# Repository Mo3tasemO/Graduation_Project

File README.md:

# Graduation Project

This repository will be for the Graduation Project.

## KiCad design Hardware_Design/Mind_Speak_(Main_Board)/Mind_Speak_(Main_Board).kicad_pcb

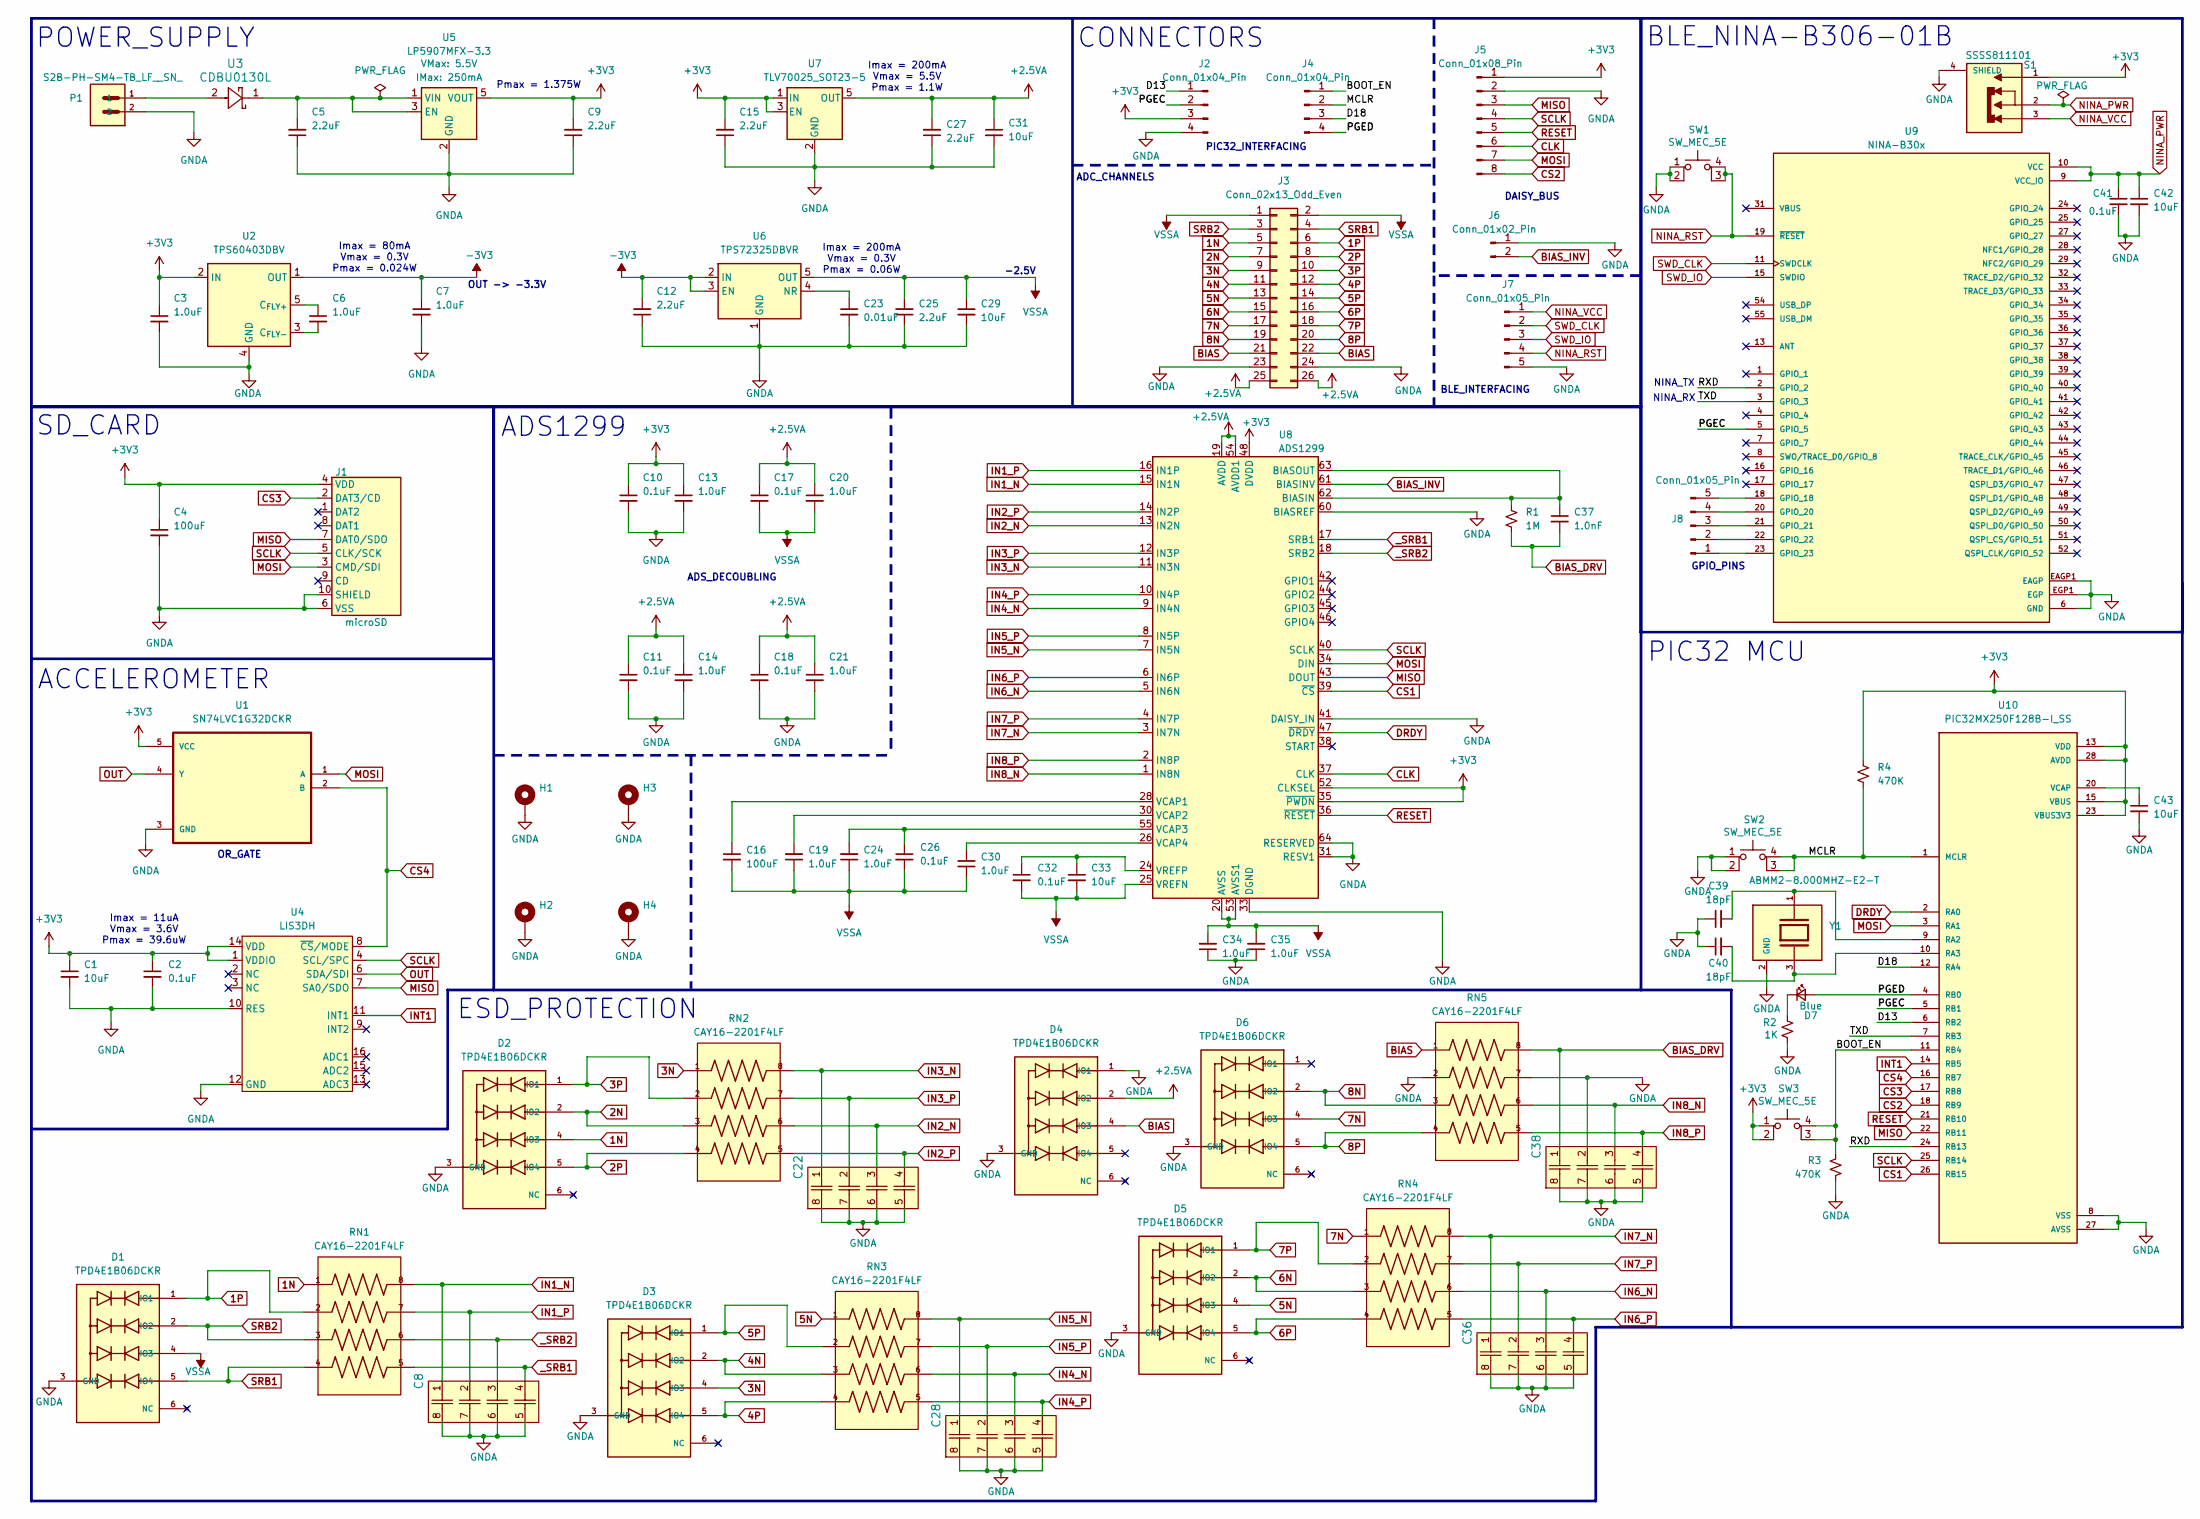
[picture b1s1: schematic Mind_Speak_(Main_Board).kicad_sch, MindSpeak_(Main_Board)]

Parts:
C1, C29, C31, C33, C42, C43: 10uF; C_0603_1608Metric; Voltage 10V; Tolerance 20%
C2, C10, C11, C17, C18, C26, C32, C41: 0.1uF; C_0402_1005Metric; Voltage 16V; Tolerance 10%
C3, C6, C7, C13, C14, C19, C20, C21, C24, C30, C34, C35: 1.0uF; C_0402_1005Metric; Voltage 16V; Tolerance 10%
C4, C16: 100uF; C_1206_3216Metric; Voltage 10V; Tolerance 20%
C5, C9, C12, C15, C25, C27: 2.2uF; C_0402_1005Metric; Voltage 10V; Tolerance 10%
C8, C22, C28, C36, C38: 0.001uF; CKCL44_TDK
C23: 0.01uF; C_0402_1005Metric; Voltage 25V; Tolerance 10%
C37: 1.0nF; C_0402_1005Metric; Voltage 50V; Tolerance 10%
C39, C40: 18pF; C_0402_1005Metric; Voltage 50V; Tolerance 5%
D1, D2, D3, D4, D5, D6: TPD4E1B06DCKR; TVS_TPD4E1B06DCKR; PARTREV C
D7: Blue; LED_0603_1608Metric_Blue
H1, H2, H3, H4: MountingHole_Pad; MountingHole_3.2mm_M3_Pad
J1: microSD; CUI_MSD-1-A
J2, J4: Conn_01x04_Pin; PinHeader_1x04_P2.54mm_Vertical
J3: Conn_02x13_Odd_Even; PinHeader_2x13_P2.54mm_Horizontal
J5: Conn_01x08_Pin; PinHeader_1x08_P2.54mm_Vertical
J6: Conn_01x02_Pin; PinHeader_1x02_P2.54mm_Vertical
J7, J8: Conn_01x05_Pin; PinHeader_1x05_P2.54mm_Vertical
P1: S2B-PH-SM4-TB_LF__SN_; JST_S2B-PH-SM4-TB_LF__SN_
R1: 1M; R_0402_1005Metric
R2: 1K; R_0402_1005Metric
R3, R4: 470K; R_0402_1005Metric
RN1, RN2, RN3, RN4, RN5: CAY16-2201F4LF; RESCAF80P320X160X60-8N
S1: SSSS811101; SW_SSSS811101; PARTREV N/A
SW1, SW2, SW3: SW_MEC_5E; SW_Push_1P1T_NO_Vertical_Wuerth_434133025816
U1: SN74LVC1G32DCKR; SOT65P210X110-5N
U2: TPS60403DBV; SOT-23-5
U3: CDBU0130L; CDBU
U4: LIS3DH; ST_LGA-16_3x3mm_P0.5mm_5x3
U5: LP5907MFX-3.3; SOT23-5
U6: TPS72325DBVR; SOT-23-5
U7: TLV70025_SOT23-5; SOT-23-5
U8: ADS1299; TQFP-64_10x10mm_P0.5mm
U9: NINA-B30x; XCVR_NINA-B306-00B; PARTREV R07
U10: PIC32MX250F128B-I_SS; SOP65P780X200-28N
Y1: ABMM2-8.000MHZ-E2-T; XTAL_ABMM2-8.000MHZ-E2-T; PARTREV 01.18.13

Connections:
1N: D2.4 (IO3), J3.5, RN1.1
1P: D1.1 (IO1), J3.6, RN1.2
2N: D2.2 (IO2), J3.7, RN2.3
2P: D2.5 (IO4), J3.8, RN2.4
3N: D3.4 (IO3), J3.9, RN2.1
3P: D2.1 (IO1), J3.10, RN2.2
4N: D3.2 (IO2), J3.11, RN3.3
4P: D3.5 (IO4), J3.12, RN3.4
5N: D5.4 (IO3), J3.13, RN3.1
5P: D3.1 (IO1), J3.14, RN3.2
6N: D5.2 (IO2), J3.15, RN4.3
6P: D5.5 (IO4), J3.16, RN4.4
7N: D6.4 (IO3), J3.17, RN4.1
7P: D5.1 (IO1), J3.18, RN4.2
8N: D6.2 (IO2), J3.19, RN5.3
8P: D6.5 (IO4), J3.20, RN5.4
+2.5VA: C11.1, C14.1, C17.1, C18.1, C20.1, C21.1, C27.2, C31.1, D4.2 (IO2), J3.25, J3.26, U7.5 (OUT), U8.19 (AVDD), U8.21 (AVDD), U8.22 (AVDD), U8.54 (AVDD1), U8.56 (AVDD), U8.59 (AVDD)
+3V3: C1.1, C2.1, C3.1, C4.1, C9.2, C10.1, C13.1, C15.2, J1.4 (VDD), J2.3, J5.1, R4.2, S1.1, SW3.1, SW3.2, U1.5 (VCC), U2.2 (IN), U4.1 (VDDIO), U4.14 (VDD), U5.5 (VOUT), U7.1 (IN), U7.3 (EN), U8.35 (~PWDN), U8.48 (DVDD), U8.50 (DVDD), U8.52 (CLKSEL), U10.13 (VDD), U10.15 (VBUS), U10.23 (VBUS3V3), U10.28 (AVDD)
-3V3: C7.1, C12.2, U2.1 (OUT), U6.2 (IN), U6.3 (EN)
/BOOT_EN: J4.1, R3.2, SW3.3 (K), SW3.4 (A), U10.11 (RB4)
/D13: J2.1, U10.6 (RB2)
/D18: J4.3, U10.12 (RA4)
/MCLR: J4.2, R4.1, SW2.3 (K), SW2.4 (A), U10.1 (MCLR)
/PGEC: J2.2, U9.5 (GPIO_5), U10.5 (RB1)
/PGED: D7.2 (A), J4.4, U10.4 (RB0)
/RXD: U9.2 (GPIO_2), U10.24 (RB13)
/TXD: U9.3 (GPIO_3), U10.7 (RB3)
BIAS: D4.4 (IO3), J3.21, J3.22, RN5.1
BIAS_DRV: C37.2, C38.1, R1.1, RN5.8
BIAS_INV: J6.2, U8.61 (BIASINV)
CLK: J5.6, U8.37 (CLK)
CS1: U8.39 (~CS), U10.26 (RB15)
CS2: J5.8, U10.18 (RB9)
CS3: J1.2 (DAT3/CD), U10.17 (RB8)
CS4: U1.2 (B), U4.8 (~CS/MODE), U10.16 (RB7)
DRDY: U8.47 (~DRDY), U10.2 (RA0)
GNDA: C1.2, C2.2, C3.2, C4.2, C5.1, C7.2, C8.5, C8.6, C8.7, C8.8, C9.1, C10.2, C11.2, C12.1, C13.2, C14.2, C15.1, C18.2, C21.2, C22.5, C22.6, C22.7, C22.8, C23.2, C25.1, C27.1, C28.5, C28.6, C28.7, C28.8, C29.2, C31.2, C34.1, C35.1, C36.5, C36.6, C36.7, C36.8, C38.2, C38.5, C38.6, C38.7, C38.8, C39.1, C40.1, C41.2, C42.2, C43.2, D1.3 (GND), D2.3 (GND), D3.3 (GND), D4.1 (IO1), D4.3 (GND), D5.3 (GND), D6.3 (GND), H1.1 (1_1), H2.1 (1_1), H3.1 (1_1), H4.1 (1_1), J1.6 (VSS), J1.10 (SHIELD), J2.4, J3.23, J3.24, J5.2, J6.1, J7.5, P1.2, R2.1, R3.1, RN5.2, RN5.7, S1.4 (SHIELD_4), SW1.1, SW1.2, SW2.1, SW2.2, U1.3 (GND), U2.4 (GND), U4.5 (GND), U4.10 (RES), U4.12 (GND), U5.2 (GND), U6.1 (GND), U7.2 (GND), U8.31 (RESV1), U8.33 (DGND), U8.41 (DAISY_IN), U8.49 (DGND), U8.51 (DGND), U8.60 (BIASREF), U8.64 (RESERVED), U9.6 (GND), U9.12 (GND), U9.14 (GND), U9.26 (GND), U9.30 (GND), U9.53 (GND), U9.EAGP1 (EAGP), U9.EAGP2 (EAGP), U9.EAGP3 (EAGP), U9.EAGP4 (EAGP), U9.EGP1 (EGP), U9.EGP2 (EGP), U9.EGP3 (EGP), U9.EGP4 (EGP), U9.EGP5 (EGP), U9.EGP6 (EGP), U9.EGP7 (EGP), U9.EGP8 (EGP), U9.EGP9 (EGP), U9.EGP10 (EGP), U9.EGP11 (EGP), U9.EGP12 (EGP), U10.8 (VSS), U10.19 (VSS), U10.27 (AVSS), Y1.2 (GND), Y1.4 (GND)
IN1_N: C8.1, RN1.8, U8.15 (IN1N)
IN1_P: C8.2, RN1.7, U8.16 (IN1P)
IN2_N: C22.3, RN2.6, U8.13 (IN2N)
IN2_P: C22.4, RN2.5, U8.14 (IN2P)
IN3_N: C22.1, RN2.8, U8.11 (IN3N)
IN3_P: C22.2, RN2.7, U8.12 (IN3P)
IN4_N: C28.3, RN3.6, U8.9 (IN4N)
IN4_P: C28.4, RN3.5, U8.10 (IN4P)
IN5_N: C28.1, RN3.8, U8.7 (IN5N)
IN5_P: C28.2, RN3.7, U8.8 (IN5P)
IN6_N: C36.3, RN4.6, U8.5 (IN6N)
IN6_P: C36.4, RN4.5, U8.6 (IN6P)
IN7_N: C36.1, RN4.8, U8.3 (IN7N)
IN7_P: C36.2, RN4.7, U8.4 (IN7P)
IN8_N: C38.3, RN5.6, U8.1 (IN8N)
IN8_P: C38.4, RN5.5, U8.2 (IN8P)
INT1: U4.11 (INT1), U10.14 (RB5)
MISO: J1.7 (DAT0/SDO), J5.3, U4.7 (SA0/SDO), U8.43 (DOUT), U10.22 (RB11)
MOSI: J1.3 (CMD/SDI), J5.7, U1.1 (A), U8.34 (DIN), U10.3 (RA1)
NINA_PWR: C41.1, C42.1, S1.2, U9.9 (VCC_IO), U9.10 (VCC)
NINA_RST: J7.4, SW1.3 (K), SW1.4 (A), U9.19 (~RESET)
NINA_VCC: J7.1, S1.3
unnamed: D7.1 (K), R2.2
unnamed: J8.1, U9.23 (GPIO_23)
unnamed: J8.2, U9.22 (GPIO_22)
unnamed: J8.3, U9.21 (GPIO_21)
unnamed: J8.4, U9.20 (GPIO_20)
unnamed: J8.5, U9.18 (GPIO_18)
unnamed: P1.1, U3.2
unnamed: C6.1, U2.5 (C_{FLY+})
unnamed: C6.2, U2.3 (C_{FLY-})
unnamed: C5.2, U3.1, U5.1 (VIN), U5.3 (EN)
unnamed: C23.1, U6.4 (NR)
unnamed: C37.1, R1.2, U8.62 (BIASIN), U8.63 (BIASOUT)
unnamed: C16.1, U8.28 (VCAP1)
unnamed: C19.2, U8.30 (VCAP2)
unnamed: C24.2, C26.1, U8.55 (VCAP3)
unnamed: C30.2, U8.26 (VCAP4)
unnamed: C32.1, C33.1, U8.24 (VREFP)
unnamed: C39.2, U10.9 (RA2), Y1.1
unnamed: C40.2, U10.10 (RA3), Y1.3
unnamed: C43.1, U10.20 (VCAP)
OUT: U1.4 (Y), U4.6 (SDA/SDI)
RESET: J5.5, U8.36 (~RESET), U10.21 (RB10)
SCLK: J1.5 (CLK/SCK), J5.4, U4.4 (SCL/SPC), U8.40 (SCLK), U10.25 (RB14)
SRB1: D1.5 (IO4), J3.4, RN1.4
SRB2: D1.2 (IO2), J3.3, RN1.3
SWD_CLK: J7.2, U9.11 (SWDCLK)
SWD_IO: J7.3, U9.15 (SWDIO)
VSSA: C16.2, C17.2, C19.1, C20.2, C24.1, C25.2, C26.2, C29.1, C30.1, C32.2, C33.2, C34.2, C35.2, D1.4 (IO3), J3.1, J3.2, U6.5 (OUT), U8.20 (AVSS), U8.23 (AVSS), U8.25 (VREFN), U8.32 (AVSS), U8.53 (AVSS1), U8.57 (AVSS), U8.58 (AVSS)
_SRB1: C8.4, RN1.5, U8.17 (SRB1)
_SRB2: C8.3, RN1.6, U8.18 (SRB2)

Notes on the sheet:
CONNECTORS
Imax = 11uA Vmax = 3.6V Pmax = 39.6uW
POWER_SUPPLY
ADC_CHANNELS
ACCELEROMETER
Imax = 200mA Vmax = 5.5V Pmax = 1.1W
BLE_NINA-B306-01B
DAISY_BUS
-2.5V
ESD_PROTECTION
Pmax = 1.375W
PIC32_INTERFACING
NINA_RX
BLE_INTERFACING
ADS1299
Imax = 200mA Vmax = 0.3V Pmax = 0.06W
Imax = 80mA Vmax = 0.3V Pmax = 0.024W
SD_CARD
ADS_DECOUBLING
OR_GATE
OUT -> -3.3V
NINA_TX
GPIO_PINS
PIC32 MCU

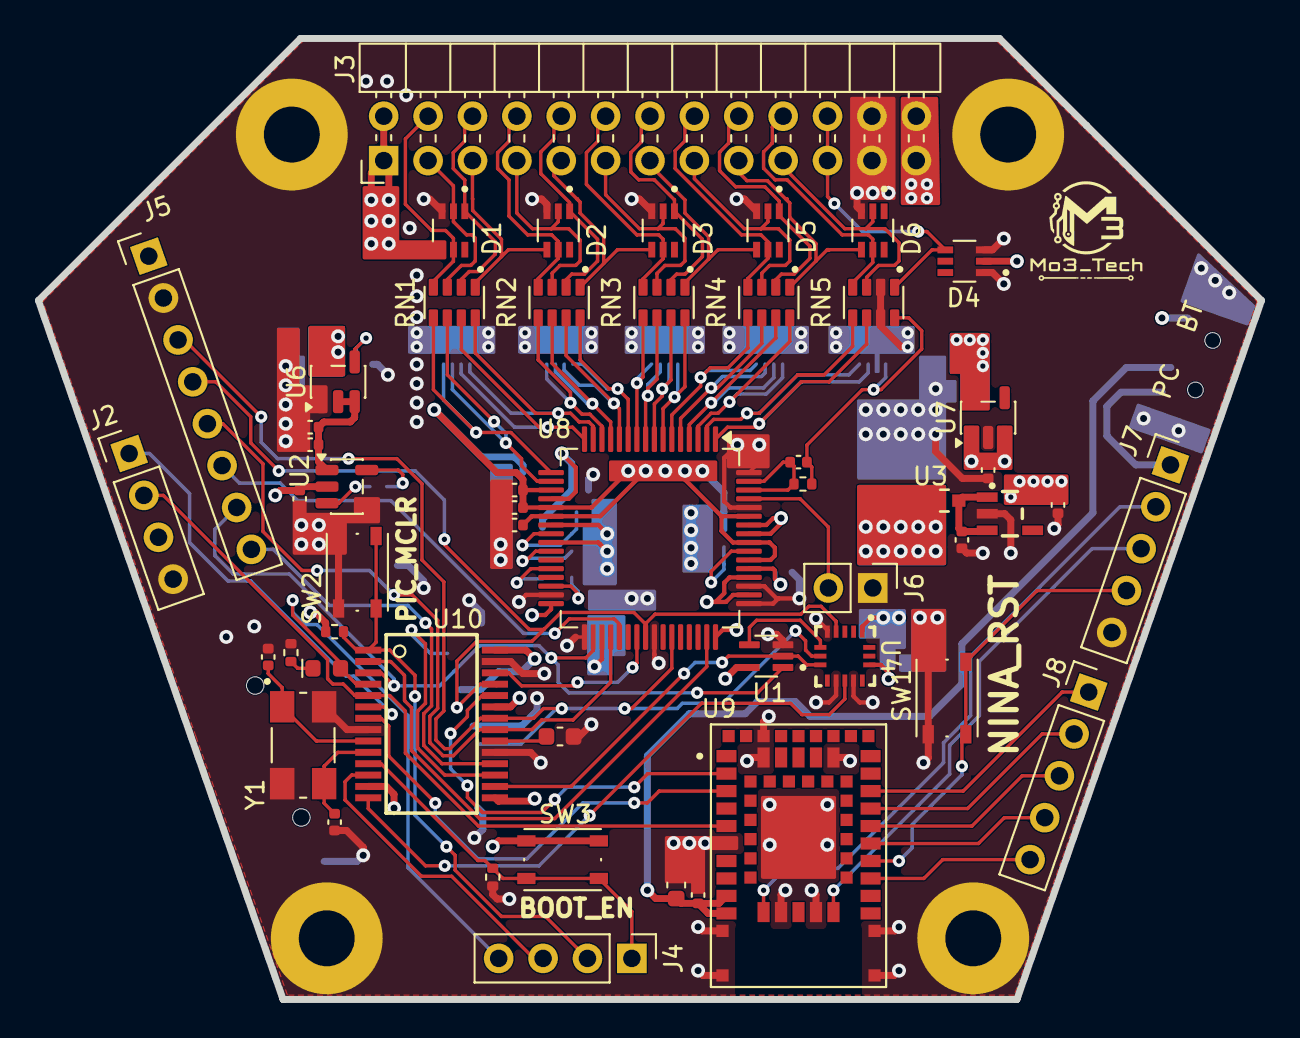
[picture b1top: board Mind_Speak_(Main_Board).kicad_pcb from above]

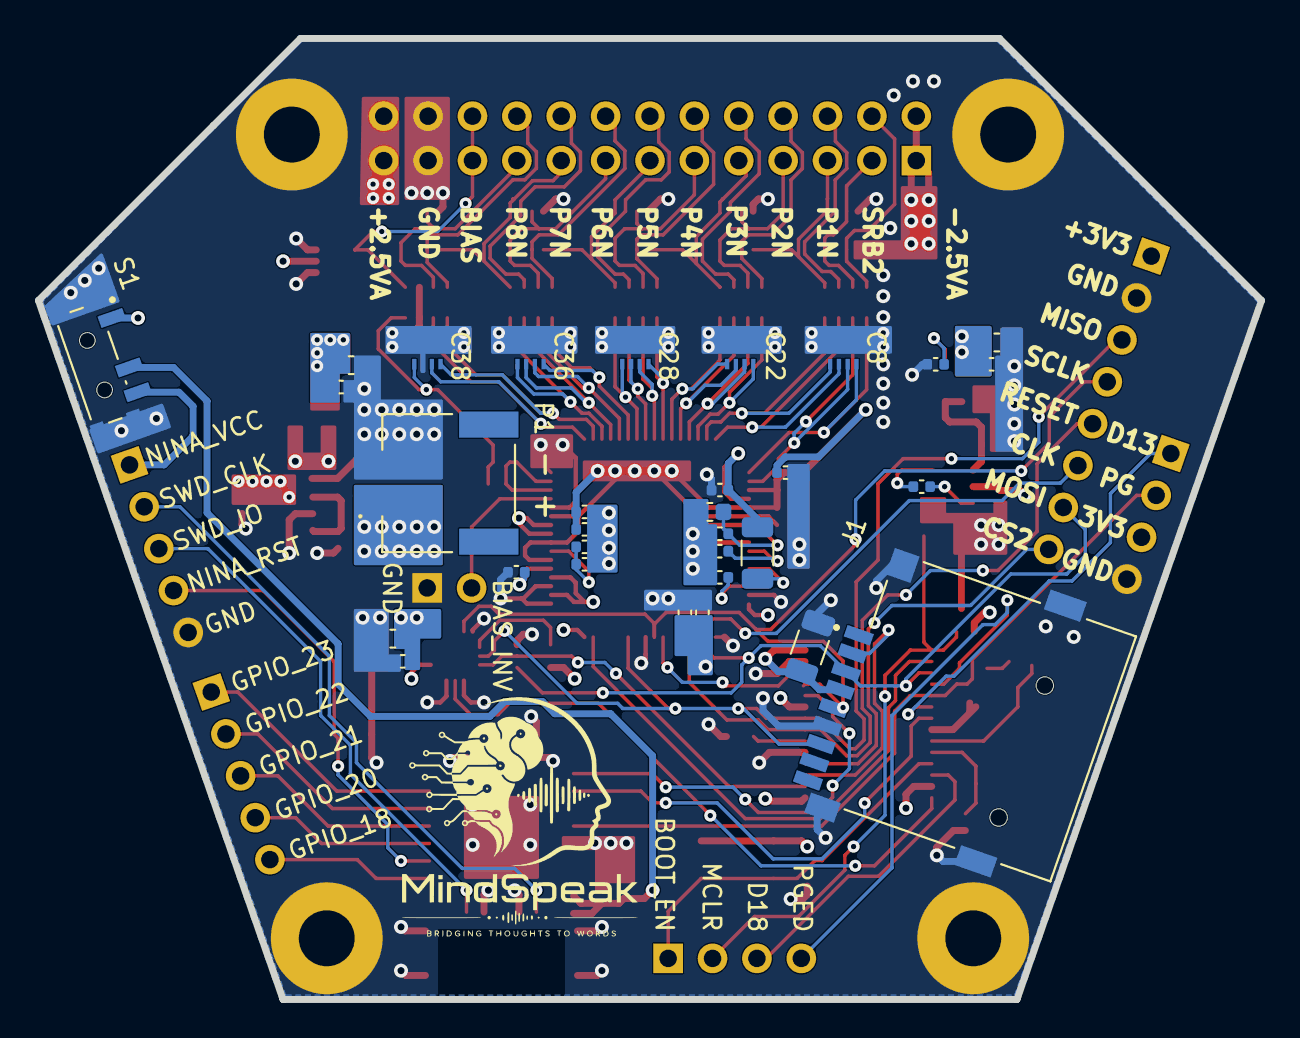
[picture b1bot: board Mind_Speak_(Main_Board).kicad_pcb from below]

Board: 4 copper layers, 70.0 x 55.0 mm, 87 parts (31 on the bottom side), 89 nets.

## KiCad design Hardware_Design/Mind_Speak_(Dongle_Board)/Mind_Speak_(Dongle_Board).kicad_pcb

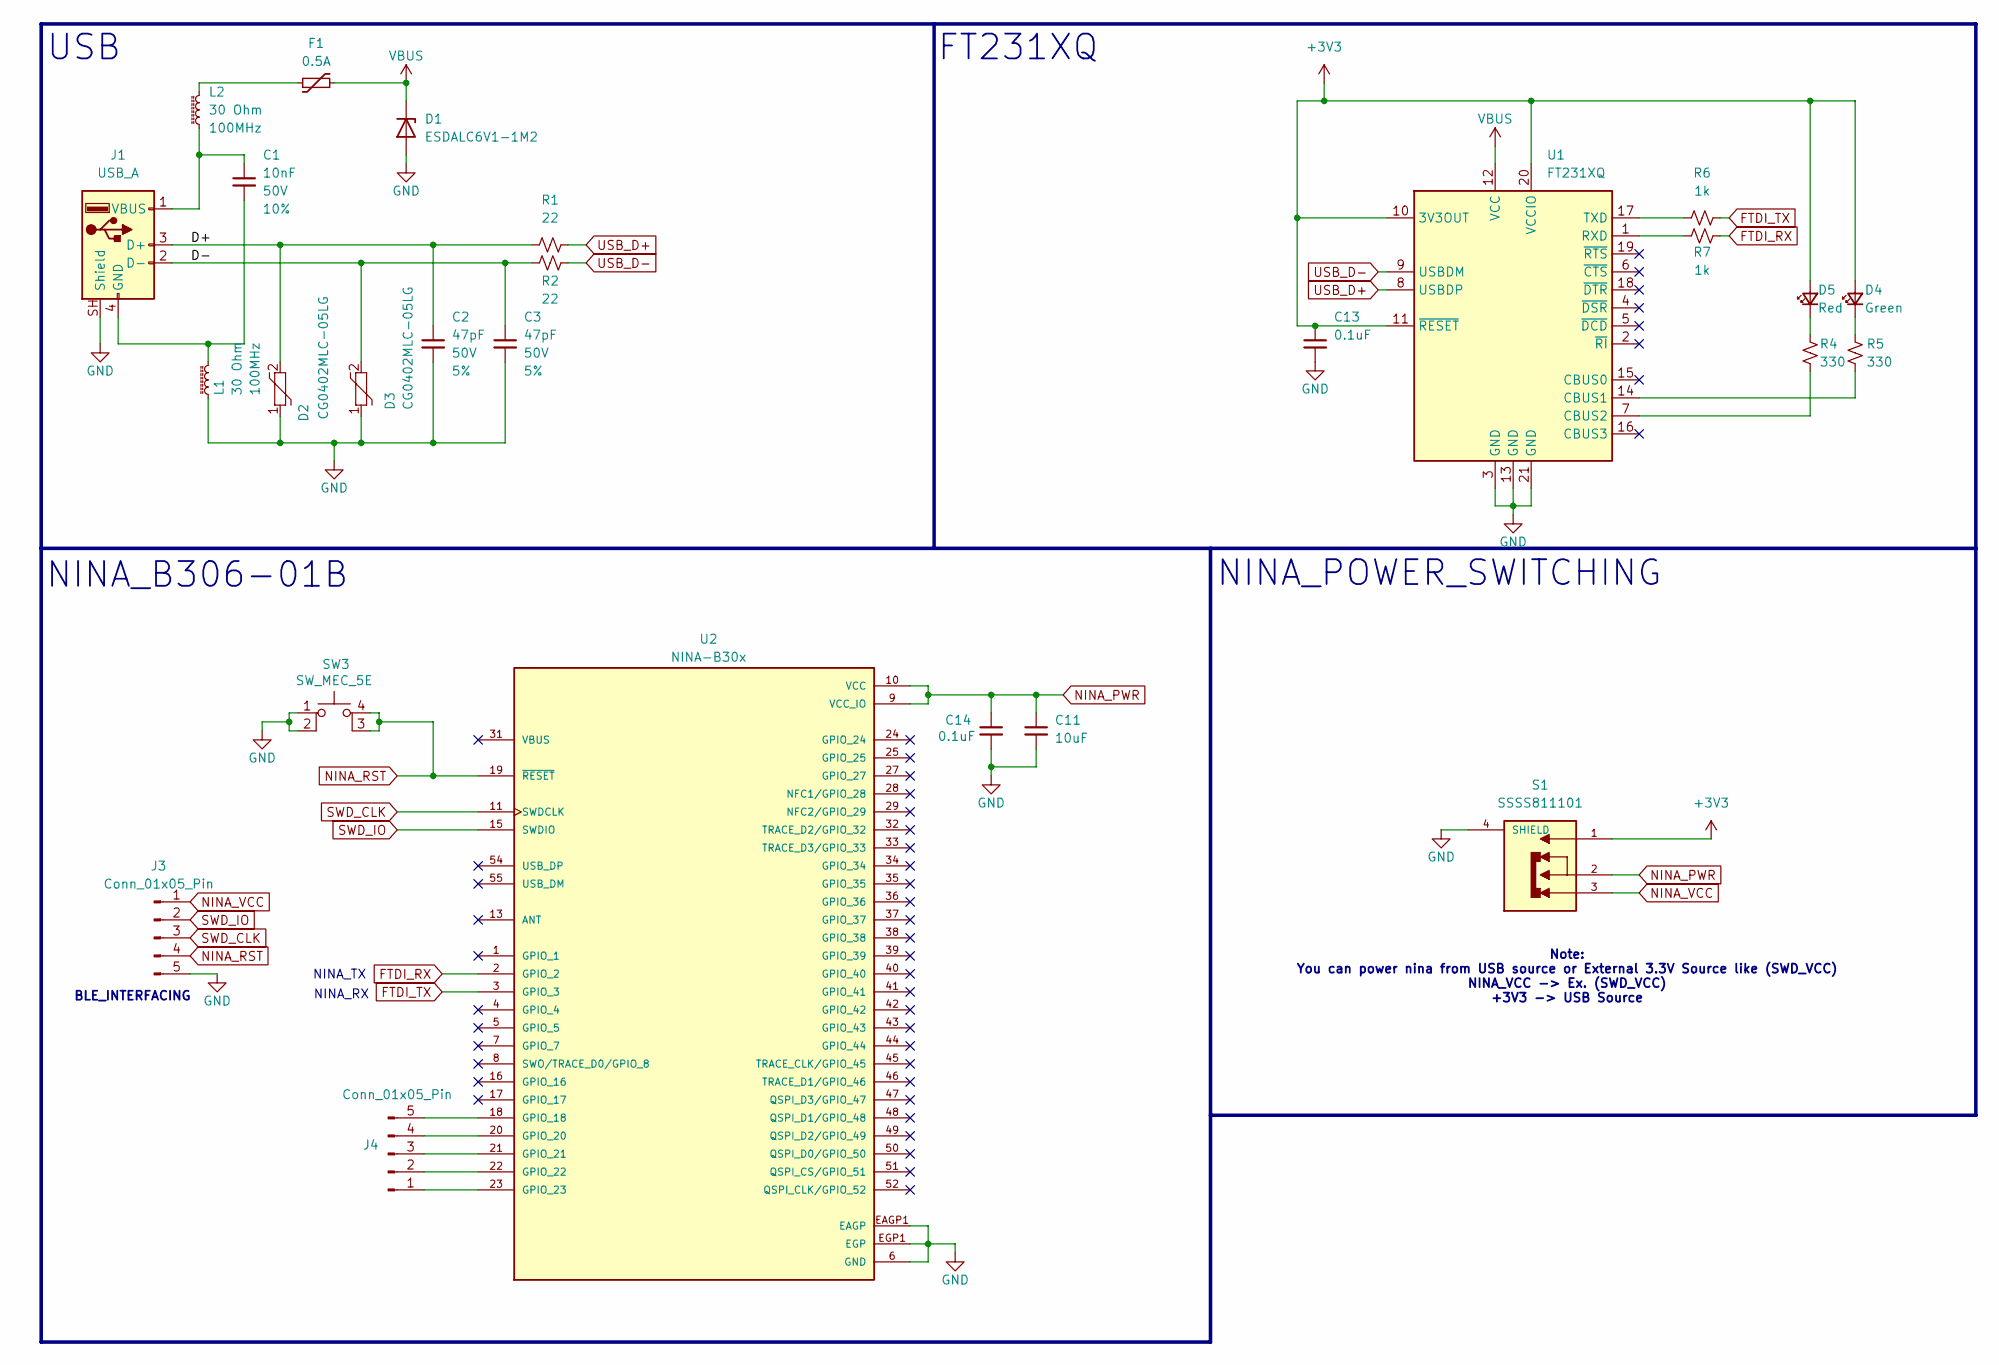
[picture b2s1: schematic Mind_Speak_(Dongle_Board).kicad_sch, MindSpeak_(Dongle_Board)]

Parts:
C1: 10nF; C_0402_1005Metric; Voltage 50V; Tolerance 10%
C2, C3: 47pF; C_0402_1005Metric; Voltage 50V; Tolerance 5%
C11: 10uF; C_0603_1608Metric; Voltage 10V; Tolerance 20%
C13, C14: 0.1uF; C_0402_1005Metric; Voltage 16V; Tolerance 10%
D1: ESDALC6V1-1M2; D_SOD-882
D2, D3: CG0402MLC-05LG
D4: Green; LED_0603_1608Metric_Green
D5: Red; LED_0603_1608Metric_Red
F1: 0.5A; 1812
J1: USB_A; MOLEX_48037-1000
J3, J4: Conn_01x05_Pin; PinHeader_1x05_P2.54mm_Vertical
L1, L2: 30 Ohm; C_0402_1005Metric
R1, R2: 22; R_0402_1005Metric
R4, R5: 330; R_0402_1005Metric
R6, R7: 1k; R_0402_1005Metric
S1: SSSS811101; SW_SSSS811101; PARTREV N/A
SW3: SW_MEC_5E; SW_Push_1P1T_NO_Vertical_Wuerth_434133025816
U1: FT231XQ; QFN-20-1EP_4x4mm_P0.5mm_EP2.5x2.5mm
U2: NINA-B30x; XCVR_NINA-B306-00B; PARTREV R07

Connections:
+3V3: C13.1, D4.2 (A), D5.2 (A), S1.1, U1.10 (3V3OUT), U1.11 (~RESET), U1.20 (VCCIO)
/D+: C2.1, D2.2, J1.3 (D+), R1.1
/D-: C3.1, D3.2, J1.2 (D-), R2.1
FTDI_RX: R7.2, U2.2 (GPIO_2)
FTDI_TX: R6.2, U2.3 (GPIO_3)
GND: C2.2, C3.2, C11.2, C13.2, C14.2, D1.2 (A), D2.1, D3.1, J1.SH (Shield), J3.5, L1.1, S1.4 (SHIELD_4), SW3.1, SW3.2, U1.3 (GND), U1.13 (GND), U1.21 (GND), U2.6 (GND), U2.12 (GND), U2.14 (GND), U2.26 (GND), U2.30 (GND), U2.53 (GND), U2.EAGP1 (EAGP), U2.EAGP2 (EAGP), U2.EAGP3 (EAGP), U2.EAGP4 (EAGP), U2.EGP1 (EGP), U2.EGP2 (EGP), U2.EGP3 (EGP), U2.EGP4 (EGP), U2.EGP5 (EGP), U2.EGP6 (EGP), U2.EGP7 (EGP), U2.EGP8 (EGP), U2.EGP9 (EGP), U2.EGP10 (EGP), U2.EGP11 (EGP), U2.EGP12 (EGP)
NINA_PWR: C11.1, C14.1, S1.2, U2.9 (VCC_IO), U2.10 (VCC)
NINA_RST: J3.4, SW3.3 (K), SW3.4 (A), U2.19 (~RESET)
NINA_VCC: J3.1, S1.3
unnamed: D4.1 (K), R5.2
unnamed: D5.1 (K), R4.2
unnamed: F1.1, L2.2
unnamed: C1.2, J1.4 (GND), L1.2
unnamed: C1.1, J1.1 (VBUS), L2.1
unnamed: J4.1, U2.23 (GPIO_23)
unnamed: J4.2, U2.22 (GPIO_22)
unnamed: J4.3, U2.21 (GPIO_21)
unnamed: J4.4, U2.20 (GPIO_20)
unnamed: J4.5, U2.18 (GPIO_18)
unnamed: R5.1, U1.14 (CBUS1)
unnamed: R4.1, U1.7 (CBUS2)
unnamed: R7.1, U1.1 (RXD)
unnamed: R6.1, U1.17 (TXD)
SWD_CLK: J3.3, U2.11 (SWDCLK)
SWD_IO: J3.2, U2.15 (SWDIO)
USB_D+: R1.2, U1.8 (USBDP)
USB_D-: R2.2, U1.9 (USBDM)
VBUS: D1.1 (K), F1.2, U1.12 (VCC)

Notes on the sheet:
Note: You can power nina from USB source or External 3.3V Source like (SWD_VCC) NINA_VCC -> Ex. (SWD_VCC) +3V3 -> USB Source
NINA_B306-01B
FT231XQ
BLE_INTERFACING
NINA_POWER_SWITCHING
NINA_TX
NINA_RX
USB

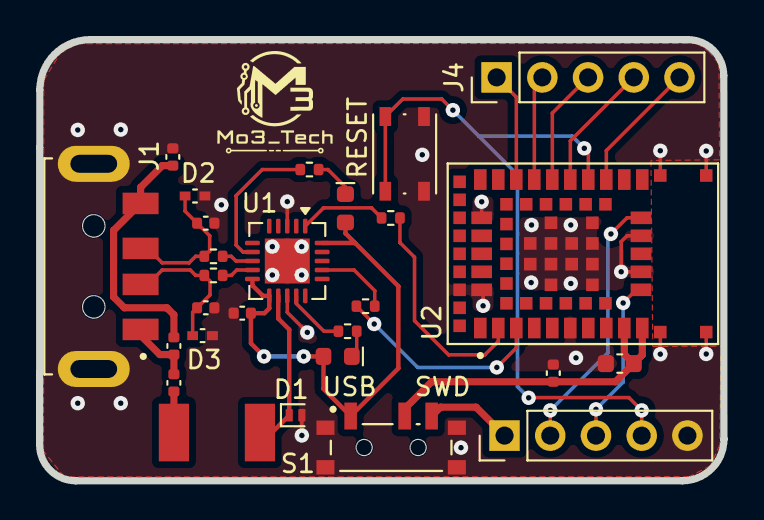
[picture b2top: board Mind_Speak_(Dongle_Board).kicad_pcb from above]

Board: 2 copper layers, 38.0 x 24.5 mm, 28 parts (0 on the bottom side), 28 nets.

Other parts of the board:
G*: LOGO; MindSpeak_Logo
